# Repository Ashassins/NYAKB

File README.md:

# NYAKB: Not Your Average Keyboard
ECE 477 Project

NYAKB is a multimedia keyboard with hot swappable modules to enable flexibility for the users by allowing them to select the right keyboard layout for the task at hand. The product features a base keyboard with a familiar form factor, as well as modules which can be added and removed with a standard hot plug connector without interrupting the functionality of the rest of the keyboard. We will be making a display module and in the future other modules such as macropads, numpads, or rotary encoders could be added using the same connector to extend the functionality of the keyboard.

Project Website: https://engineering.purdue.edu/477grp3/

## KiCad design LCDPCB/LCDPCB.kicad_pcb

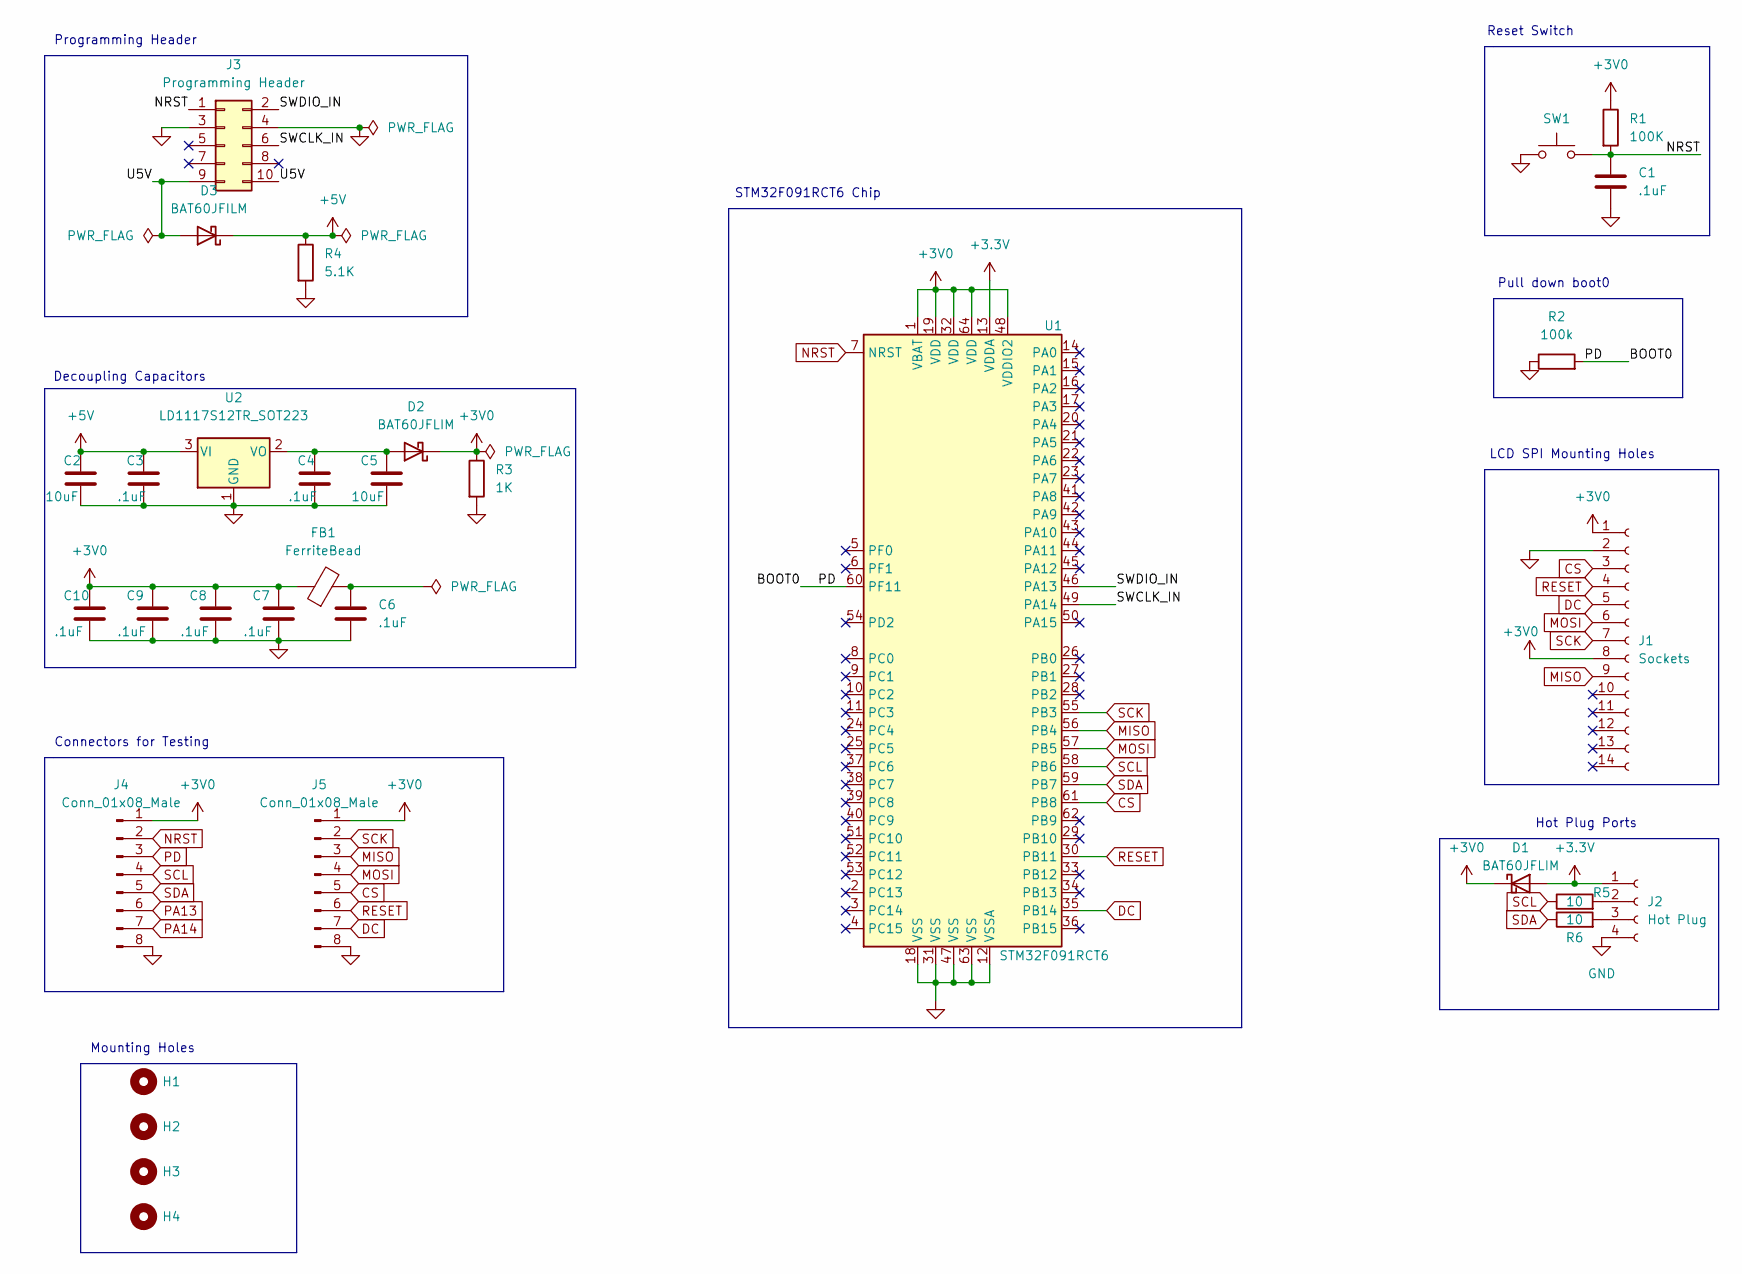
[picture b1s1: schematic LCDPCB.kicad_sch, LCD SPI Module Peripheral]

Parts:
C1, C3, C4, C6, C7, C8, C9, C10: .1uF
C2: 10uF; new10uf
C5: 10uF
D1, D2: BAT60JFLIM; BAT60JFILM
D3: BAT60JFILM
FB1: FerriteBead; Ferrite
H1, H2, H3, H4: MountingHole; MountingHole_2.2mm_M2_ISO7380
J1: Sockets; PinSocket_1x14_P2.54mm_Vertical
J2: Hot Plug; PinSocket_1x04_P2.54mm_Vertical
J3: Programming Header; PinSocket_2x05_P2.54mm_Vertical
J4, J5: Conn_01x08_Male; PinHeader_1x08_P2.54mm_Vertical
R1: 100K; 100k
R2: 100k
R3: 1K; 1k
R4: 5.1K; 5.1k
R5, R6: 10; 10R
SW1: SW_Push; Button
U1: STM32F091RCT6; STM32F091
U2: LD1117S12TR_SOT223; SOT-223-3_TabPin2

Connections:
+3.3V: D1.2 (A), J2.1, U1.13 (VDDA)
+3V0: C7.1, C8.1, C9.1, C10.1, D1.1 (K), D2.1 (K), FB1.1, J1.1, J1.8, J4.1, J5.1, R1.1, R3.1, U1.1 (VBAT), U1.19 (VDD), U1.32 (VDD), U1.48 (VDDIO2), U1.64 (VDD)
+5V: C2.1, C3.1, D3.1 (K), R4.1, U2.3 (VI)
/SWCLK_IN: J3.6, U1.49 (PA14)
/SWDIO_IN: J3.2, U1.46 (PA13)
/U5V: D3.2 (A), J3.9, J3.10
CS: J1.3, J5.5, U1.61 (PB8)
DC: J1.5, J5.7, U1.35 (PB14)
GND: C1.2, C2.2, C3.2, C4.2, C5.2, C6.2, C7.2, C8.2, C9.2, C10.2, J1.2, J2.4, J3.3, J3.4, J4.8, J5.8, R2.1, R3.2, R4.2, SW1.1, U1.12 (VSSA), U1.18 (VSS), U1.31 (VSS), U1.47 (VSS), U1.63 (VSS), U2.1 (GND)
MISO: J1.9, J5.3, U1.56 (PB4)
MOSI: J1.6, J5.4, U1.57 (PB5)
NRST: C1.1, J3.1, J4.2, R1.2, SW1.2, U1.7 (NRST)
unnamed: C4.1, C5.1, D2.2 (A), U2.2 (VO)
unnamed: C6.1, FB1.2
unnamed: J2.2, R5.2
unnamed: J2.3, R6.2
PA13: J4.6
PA14: J4.7
PD: J4.3, R2.2, U1.60 (PF11)
RESET: J1.4, J5.6, U1.30 (PB11)
SCK: J1.7, J5.2, U1.55 (PB3)
SCL: J4.4, R5.1, U1.58 (PB6)
SDA: J4.5, R6.1, U1.59 (PB7)

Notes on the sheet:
Mounting Holes
Reset Switch
STM32F091RCT6 Chip
Programming Header
Connectors for Testing
Pull down boot0
Decoupling Capacitors
Hot Plug Ports
LCD SPI Mounting Holes

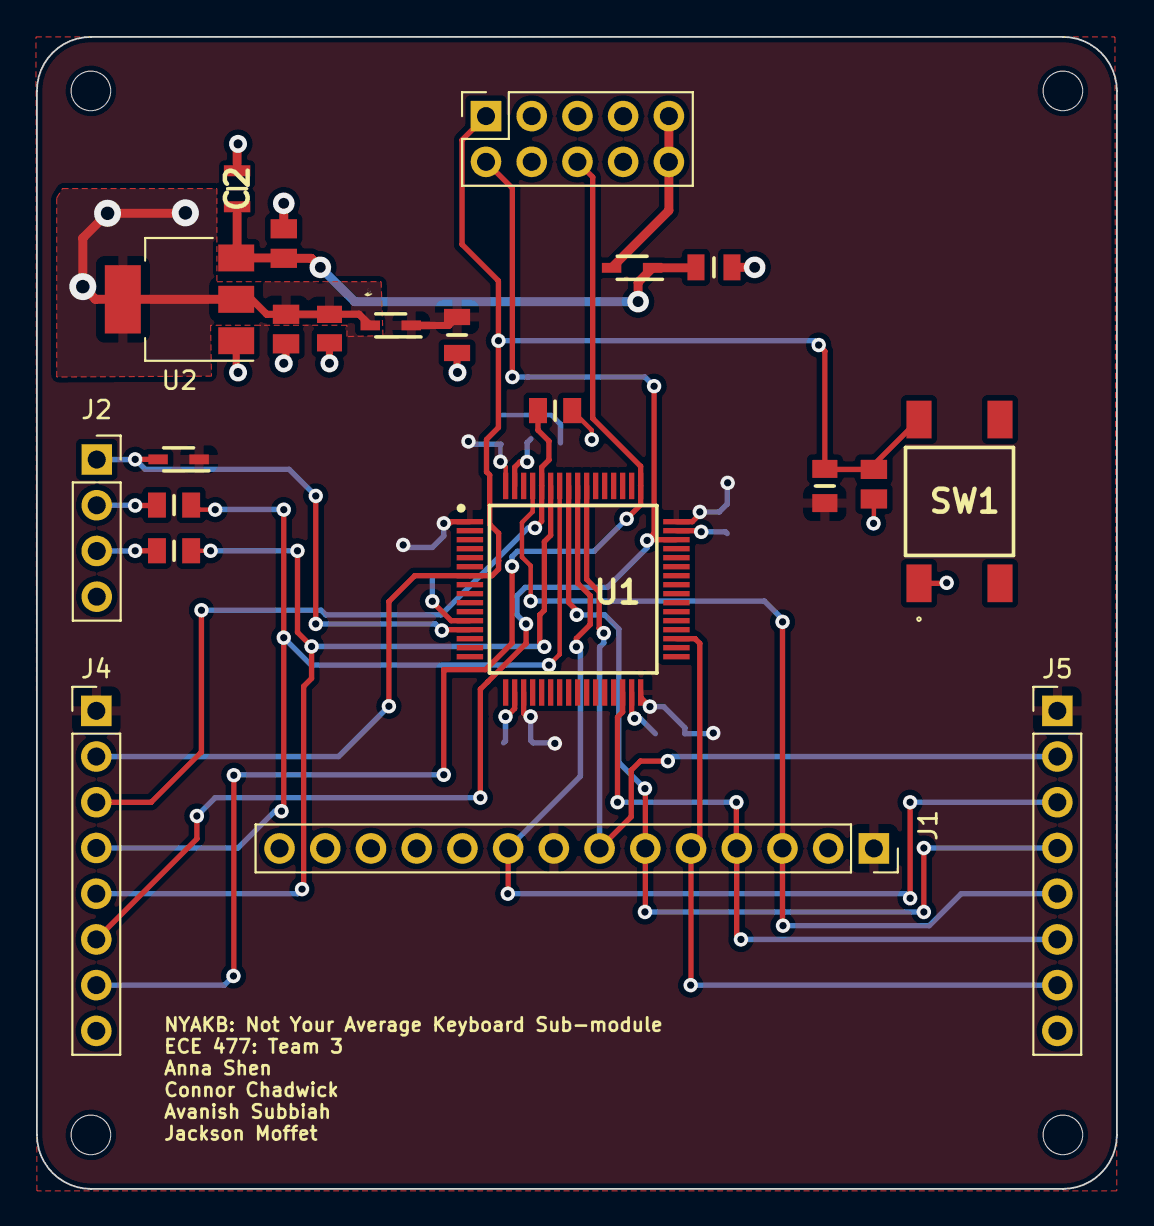
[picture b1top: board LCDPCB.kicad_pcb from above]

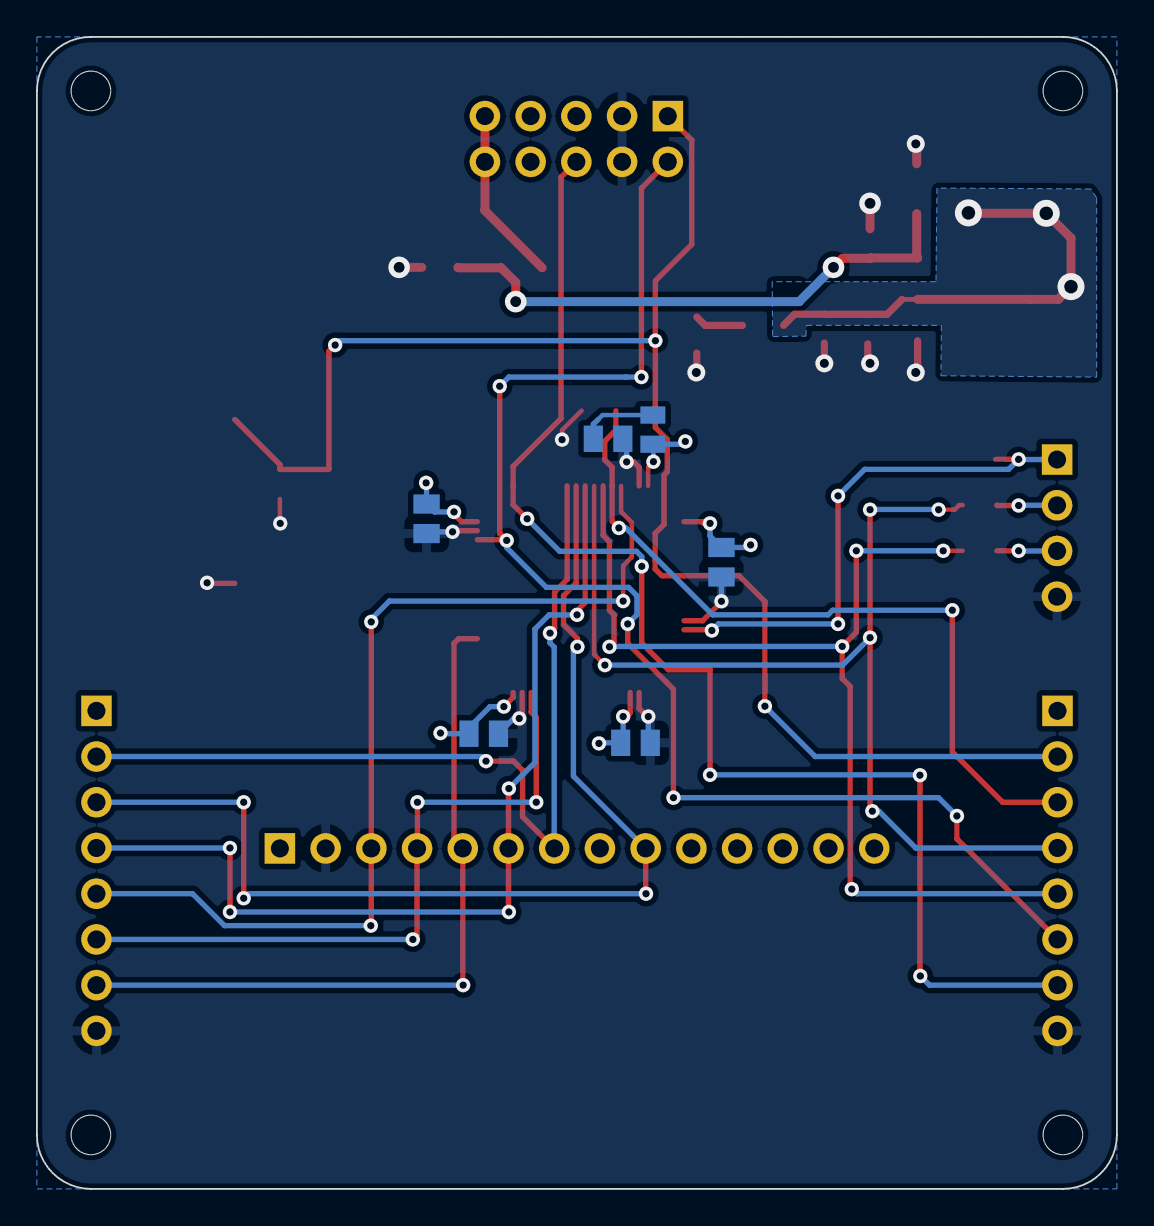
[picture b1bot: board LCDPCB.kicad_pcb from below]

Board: 2 copper layers, 60.0 x 64.0 mm, 32 parts (6 on the bottom side), 21 nets.

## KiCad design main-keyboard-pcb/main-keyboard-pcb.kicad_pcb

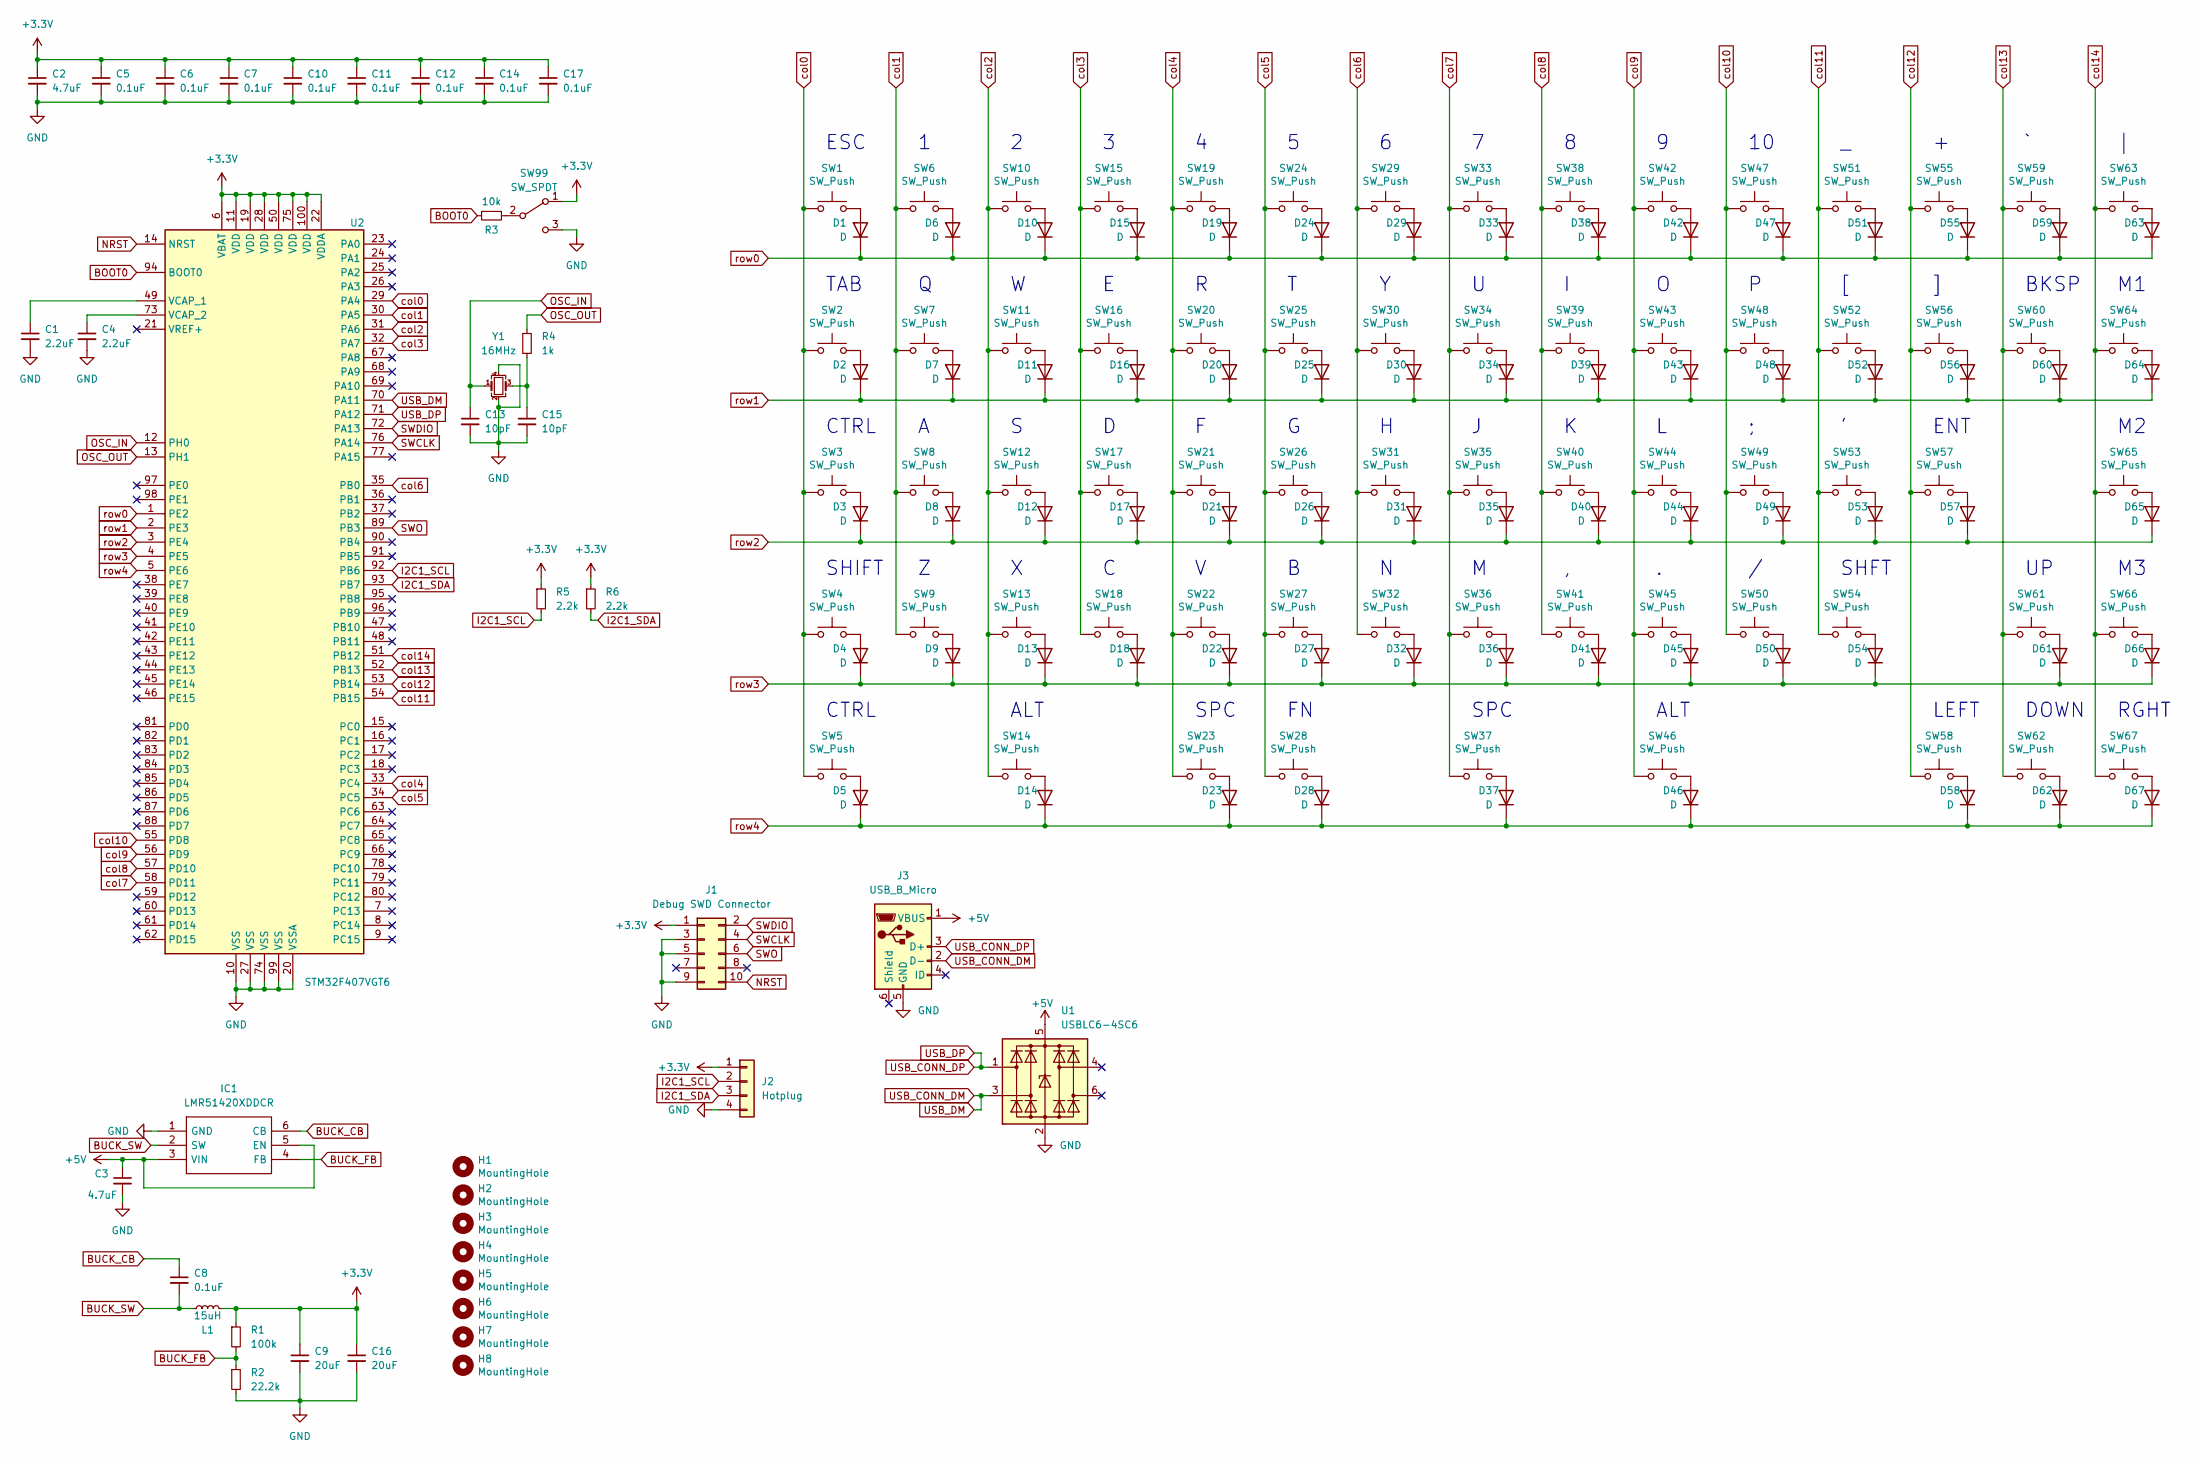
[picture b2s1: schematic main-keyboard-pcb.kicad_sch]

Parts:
C1, C4: 2.2uF; GRM155R61E225KE11D
C2, C3: 4.7uF; GRM188R61C475KAAJD
C5, C6, C7, C8, C10, C11, C12, C14, C17: 0.1uF; GRM022R61A104ME01L
C9, C16: 20uF; GRMJN7R61C206ME05D
C13, C15: 10pF; GRM0225C1C100FA03L
D1, D2, D3, D4, D5, D6, D7, D8, D9, D10, D11, D12, D13, D14, D15, D16, D17, D18, D19, D20, D21, D22, D23, D24, D25, D26, D27, D28, D29, D30, D31, D32, D33, D34, D35, D36, D37, D38, D39, D40, D41, D42, D43, D44, D45, D46, D47, D48, D49, D50, D51, D52, D53, D54, D55, D56, D57, D58, D59, D60, D61, D62, D63, D64, D65, D66, D67: D; 1N4148W-13-F
H1, H2, H3, H4, H5, H6, H7, H8: MountingHole; MountingHole_2.2mm_M2_Pad
IC1: LMR51420XDDCR; Manufacturer_Part_Number LMR51420XDDCR
J1: Debug SWD Connector; PinHeader_2x05_P1.27mm_Vertical_SMD
J2: Hotplug; PinHeader_1x04_P2.54mm_Vertical
J3: USB_B_Micro; USB307530A
L1: 15uH; SRP1265WA150M
R1: 100k; CHV1206AJW-104ELF
R2: 22.2k; ERJP08F2212V
R3: 10k; ERJ-UP3F1002V
R4: 1k; ERJ-UP3D1001V
R5, R6: 2.2k; ERJ-UP3F2201V
SW1, SW6, SW7, SW8, SW9, SW10, SW11, SW12, SW13, SW15, SW16, SW17, SW18, SW19, SW20, SW21, SW22, SW24, SW25, SW26, SW27, SW28, SW29, SW30, SW31, SW32, SW33, SW34, SW35, SW36, SW38, SW39, SW40, SW41, SW42, SW43, SW44, SW45, SW47, SW48, SW49, SW50, SW51, SW52, SW53, SW55, SW56, SW58, SW59, SW61, SW62, SW63, SW64, SW65, SW66, SW67: SW_Push; SW_Cherry_MX_1.00u_PCB
SW2, SW5, SW14, SW46, SW60: SW_Push; SW_Cherry_MX_1.50u_PCB
SW3, SW54: SW_Push; SW_Cherry_MX_1.75u_PCB
SW4: SW_Push; SW_Cherry_MX_2.25u_PCB
SW23: SW_Push; SW_Cherry_MX_2.00u_PCB_ReversedStabilizers
SW37: SW_Push; SW_Cherry_MX_2.75u_PCB_ReversedStabilizers
SW57: SW_Push; SW_Cherry_MX_2.25u_PCB_ReversedStabilizers
SW99: SW_SPDT; SW_SPDT_PCM12
U1: USBLC6-4SC6; SOT-23-6
U2: STM32F407VGT6; LQFP-100_14x14mm_P0.5mm
Y1: 16MHz; ECS-160-10-30B-CKM-TR

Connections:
+3V3: C2.1, C5.1, C6.1, C7.1, C9.1, C10.1, C11.1, C12.1, C14.1, C16.1, C17.1, J1.1, J2.1, L1.2, R1.1, R5.1, R6.1, SW99.1 (A), U2.6 (VBAT), U2.11 (VDD), U2.19 (VDD), U2.22 (VDDA), U2.28 (VDD), U2.50 (VDD), U2.75 (VDD), U2.100 (VDD)
+5V: C3.1, IC1.3 (VIN), IC1.5 (EN), J3.1 (VBUS), U1.5 (VBUS)
BOOT0: R3.2, U2.94 (BOOT0)
BUCK_CB: C8.1, IC1.6 (CB)
BUCK_FB: IC1.4 (FB), R1.2, R2.1
BUCK_SW: C8.2, IC1.2 (SW), L1.1
GND: C1.2, C2.2, C3.2, C4.2, C5.2, C6.2, C7.2, C9.2, C10.2, C11.2, C12.2, C13.2, C14.2, C15.2, C16.2, C17.2, IC1.1 (GND), J1.3, J1.5, J1.9, J2.4, J3.5 (GND), R2.2, SW99.3 (C), U1.2 (GND), U2.10 (VSS), U2.20 (VSSA), U2.27 (VSS), U2.74 (VSS), U2.99 (VSS), Y1.2, Y1.4
I2C1_SCL: J2.2, R5.2, U2.92 (PB6)
I2C1_SDA: J2.3, R6.2, U2.93 (PB7)
NRST: J1.10, U2.14 (NRST)
unnamed: C1.1, U2.49 (VCAP_1)
unnamed: C4.1, U2.73 (VCAP_2)
unnamed: C15.1, R4.2, Y1.3
unnamed: D1.2 (A), SW1.2
unnamed: D2.2 (A), SW2.2
unnamed: D3.2 (A), SW3.2
unnamed: D4.2 (A), SW4.2
unnamed: D5.2 (A), SW5.2
unnamed: D6.2 (A), SW6.2
unnamed: D7.2 (A), SW7.2
unnamed: D8.2 (A), SW8.2
unnamed: D9.2 (A), SW9.2
unnamed: D10.2 (A), SW10.2
unnamed: D11.2 (A), SW11.2
unnamed: D12.2 (A), SW12.2
unnamed: D13.2 (A), SW13.2
unnamed: D14.2 (A), SW14.2
unnamed: D15.2 (A), SW15.2
unnamed: D16.2 (A), SW16.2
unnamed: D17.2 (A), SW17.2
unnamed: D18.2 (A), SW18.2
unnamed: D19.2 (A), SW19.2
unnamed: D20.2 (A), SW20.2
unnamed: D21.2 (A), SW21.2
unnamed: D22.2 (A), SW22.2
unnamed: D23.2 (A), SW23.2
unnamed: D24.2 (A), SW24.2
unnamed: D25.2 (A), SW25.2
unnamed: D26.2 (A), SW26.2
unnamed: D27.2 (A), SW27.2
unnamed: D28.2 (A), SW28.2
unnamed: D29.2 (A), SW29.2
unnamed: D30.2 (A), SW30.2
unnamed: D31.2 (A), SW31.2
unnamed: D32.2 (A), SW32.2
unnamed: D33.2 (A), SW33.2
unnamed: D34.2 (A), SW34.2
unnamed: D35.2 (A), SW35.2
unnamed: D36.2 (A), SW36.2
unnamed: D37.2 (A), SW37.2
unnamed: D38.2 (A), SW38.2
unnamed: D39.2 (A), SW39.2
unnamed: D40.2 (A), SW40.2
unnamed: D41.2 (A), SW41.2
unnamed: D42.2 (A), SW42.2
unnamed: D43.2 (A), SW43.2
unnamed: D44.2 (A), SW44.2
unnamed: D45.2 (A), SW45.2
unnamed: D46.2 (A), SW46.2
unnamed: D47.2 (A), SW47.2
unnamed: D48.2 (A), SW48.2
unnamed: D49.2 (A), SW49.2
unnamed: D50.2 (A), SW50.2
unnamed: D51.2 (A), SW51.2
unnamed: D52.2 (A), SW52.2
unnamed: D53.2 (A), SW53.2
unnamed: D54.2 (A), SW54.2
unnamed: D55.2 (A), SW55.2
unnamed: D56.2 (A), SW56.2
unnamed: D57.2 (A), SW57.2
unnamed: D58.2 (A), SW58.2
unnamed: D59.2 (A), SW59.2
unnamed: D60.2 (A), SW60.2
unnamed: D61.2 (A), SW61.2
unnamed: D62.2 (A), SW62.2
unnamed: D63.2 (A), SW63.2
unnamed: D64.2 (A), SW64.2
unnamed: D65.2 (A), SW65.2
unnamed: D66.2 (A), SW66.2
unnamed: D67.2 (A), SW67.2
unnamed: R3.1, SW99.2 (B)
OSC_IN: C13.1, U2.12 (PH0), Y1.1
OSC_OUT: R4.1, U2.13 (PH1)
SWCLK: J1.4, U2.76 (PA14)
SWDIO: J1.2, U2.72 (PA13)
SWO: J1.6, U2.89 (PB3)
USB_CONN_DM: J3.2 (D-), U1.3 (I/O2), U2.70 (PA11)
USB_CONN_DP: J3.3 (D+), U1.1 (I/O1), U2.71 (PA12)
col0: SW1.1, SW2.1, SW3.1, SW4.1, SW5.1, U2.29 (PA4)
col1: SW6.1, SW7.1, SW8.1, SW9.1, U2.30 (PA5)
col2: SW10.1, SW11.1, SW12.1, SW13.1, SW14.1, U2.31 (PA6)
col3: SW15.1, SW16.1, SW17.1, SW18.1, U2.32 (PA7)
col4: SW19.1, SW20.1, SW21.1, SW22.1, SW23.1, U2.33 (PC4)
col5: SW24.1, SW25.1, SW26.1, SW27.1, SW28.1, U2.34 (PC5)
col6: SW29.1, SW30.1, SW31.1, SW32.1, U2.35 (PB0)
col7: SW33.1, SW34.1, SW35.1, SW36.1, SW37.1, U2.58 (PD11)
col8: SW38.1, SW39.1, SW40.1, SW41.1, U2.57 (PD10)
col9: SW42.1, SW43.1, SW44.1, SW45.1, SW46.1, U2.56 (PD9)
col10: SW47.1, SW48.1, SW49.1, SW50.1, U2.55 (PD8)
col11: SW51.1, SW52.1, SW53.1, SW54.1, U2.54 (PB15)
col12: SW55.1, SW56.1, SW57.1, SW58.1, U2.53 (PB14)
col13: SW59.1, SW60.1, SW61.1, SW62.1, U2.52 (PB13)
col14: SW63.1, SW64.1, SW65.1, SW66.1, SW67.1, U2.51 (PB12)
row0: D1.1 (K), D6.1 (K), D10.1 (K), D15.1 (K), D19.1 (K), D24.1 (K), D29.1 (K), D33.1 (K), D38.1 (K), D42.1 (K), D47.1 (K), D51.1 (K), D55.1 (K), D59.1 (K), D63.1 (K), U2.1 (PE2)
row1: D2.1 (K), D7.1 (K), D11.1 (K), D16.1 (K), D20.1 (K), D25.1 (K), D30.1 (K), D34.1 (K), D39.1 (K), D43.1 (K), D48.1 (K), D52.1 (K), D56.1 (K), D60.1 (K), D64.1 (K), U2.2 (PE3)
row2: D3.1 (K), D8.1 (K), D12.1 (K), D17.1 (K), D21.1 (K), D26.1 (K), D31.1 (K), D35.1 (K), D40.1 (K), D44.1 (K), D49.1 (K), D53.1 (K), D57.1 (K), D65.1 (K), U2.3 (PE4)
row3: D4.1 (K), D9.1 (K), D13.1 (K), D18.1 (K), D22.1 (K), D27.1 (K), D32.1 (K), D36.1 (K), D41.1 (K), D45.1 (K), D50.1 (K), D54.1 (K), D61.1 (K), D66.1 (K), U2.4 (PE5)
row4: D5.1 (K), D14.1 (K), D23.1 (K), D28.1 (K), D37.1 (K), D46.1 (K), D58.1 (K), D62.1 (K), D67.1 (K), U2.5 (PE6)

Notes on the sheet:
TAB
SPC
ESC
RGHT
ALT
ENT
LEFT
BKSP
SHIFT
CTRL
SHFT
DOWN

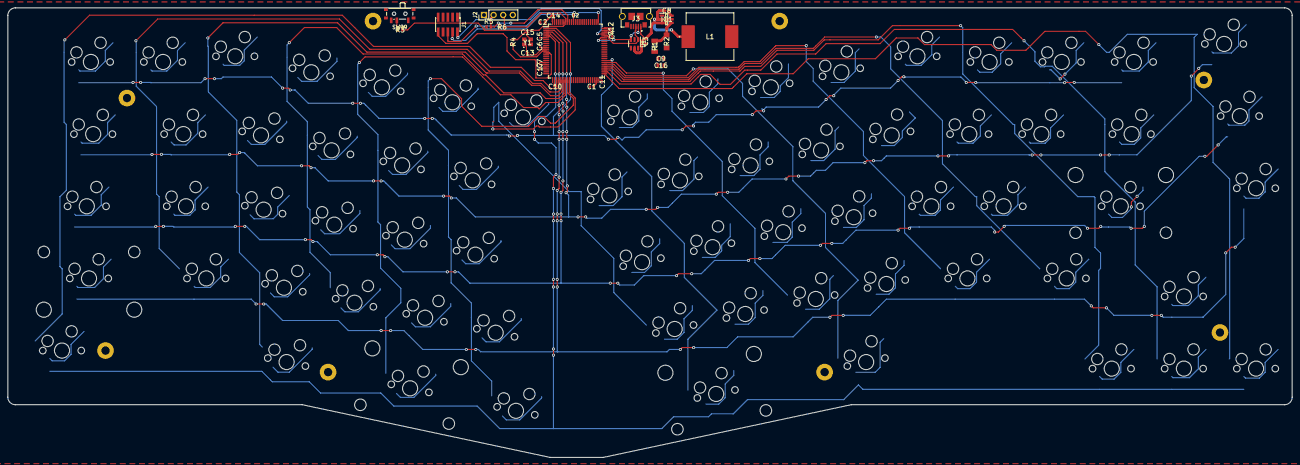
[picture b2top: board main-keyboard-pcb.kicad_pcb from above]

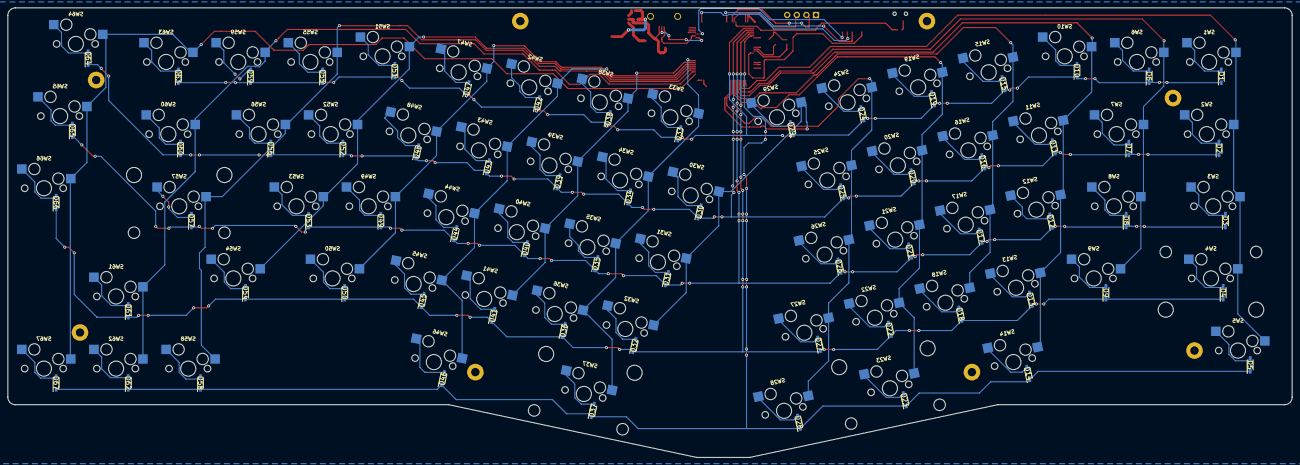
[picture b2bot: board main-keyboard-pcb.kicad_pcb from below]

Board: 4 copper layers, 339.1 x 118.7 mm, 174 parts (67 on the bottom side), 108 nets.

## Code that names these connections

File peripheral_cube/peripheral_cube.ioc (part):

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Mcu.Name=STM32F091R(B-C)Tx
Mcu.Package=LQFP64
Mcu.UserName=STM32F091RCTx
PA13.Mode=Serial_Wire
PA13.Signal=SYS_SWDIO
PA14.Mode=Serial_Wire
PA14.Signal=SYS_SWCLK
PB3.Mode=Full_Duplex_Master
PB3.Signal=SPI1_SCK
PB4.Mode=Full_Duplex_Master
PB4.Signal=SPI1_MISO
PB5.Mode=Full_Duplex_Master
PB5.Signal=SPI1_MOSI
PB8.Signal=GPIO_Output
PF0-OSC_IN.Mode=I2C
PF0-OSC_IN.Signal=I2C1_SDA
PF1-OSC_OUT.Mode=I2C
PF1-OSC_OUT.Signal=I2C1_SCL
RCC.SYSCLKFreq_VALUE=48000000
RCC.SYSCLKSource=RCC_SYSCLKSOURCE_HSI48
board=custom

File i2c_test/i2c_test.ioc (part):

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Mcu.Name=STM32F407V(E-G)Tx
Mcu.Package=LQFP100
Mcu.UserName=STM32F407VGTx
PB6.Mode=I2C
PB6.Signal=I2C1_SCL
PB7.Mode=I2C
PB7.Signal=I2C1_SDA
PH0-OSC_IN.Mode=HSE-External-Oscillator
PH0-OSC_IN.Signal=RCC_OSC_IN
PH1-OSC_OUT.Mode=HSE-External-Oscillator
PH1-OSC_OUT.Signal=RCC_OSC_OUT
RCC.HSE_VALUE=8000000
RCC.SYSCLKFreq_VALUE=168000000
RCC.SYSCLKSource=RCC_SYSCLKSOURCE_PLLCLK
board=custom

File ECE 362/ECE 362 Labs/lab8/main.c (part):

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    RCC->AHBENR |= RCC_AHBENR_GPIOBEN;
    RCC->AHBENR |= RCC_AHBENR_GPIOCEN;

    // GPIOB PB0-10 Outputs
    GPIOB->MODER &= ~0x3FFFFF; // Clear PB0-10
    GPIOB->MODER |= 0x155555;

    // GPIOC PC4-7 Outputs
    GPIOC->MODER &= ~0xFF00;
    GPIOC->MODER |= 0x5500;

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void setup_bb(void) {
    // Enable RCC to GPIOB
    RCC->AHBENR |= RCC_AHBENR_GPIOBEN;
    // Clear PB12,13,15
    GPIOB->MODER &= ~0xCF000000; // Clear PB0-10
    // GPIOB PB12,13,15 Output
    GPIOB->MODER |= 0x45000000;
    // NSS high SCK low
    GPIOB->ODR |= 1<<12;
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void init_spi2(void) {
    // Enable RCC to SPI2
    RCC->APB1ENR |= RCC_APB1ENR_SPI2EN;
    // Enable GPIO Alternate function for PB12,13,15
    // Enable RCC to GPIOB
    RCC->AHBENR |= RCC_AHBENR_GPIOBEN;
    // Clear PB12,13,15
    GPIOB->MODER &= ~0xCF000000; // Clear PB0-10
    // GPIOB PB12,13,15 Alternate Function
    GPIOB->MODER |= 0x8a000000;
    // PB12: AF0
    GPIOB->AFR[1] &= ~(0xf << (4*(12-8)));
    GPIOB->AFR[1] |=   0x0 << (4*(12-8));
    // PB13: AF0
    GPIOB->AFR[1] &= ~(0xf << (4*(13-8)));
    GPIOB->AFR[1] |=   0x0 << (4*(13-8));
    // PB15: AF0
    GPIOB->AFR[1] &= ~(0xf << (4*(15-8)));
    GPIOB->AFR[1] |=   0x0 << (4*(15-8));
    SPI2->CR1 &= ~SPI_CR1_SPE; // Clear CR1_SPE
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void setup_spi1() {
    // Enable RCC to SPI2
    RCC->APB2ENR |= RCC_APB2ENR_SPI1EN;
    // Enable GPIO Alternate function for PB12,13,15
    // Enable RCC to GPIOB
    RCC->AHBENR |= RCC_AHBENR_GPIOAEN;
    // Clear PA5,6,7,15
    GPIOA->MODER &= ~0xc000fc00; // Clear  PA5,6,7,15
    // GPIOB PB12,13,15 Alternate Function
    GPIOA->MODER |= 0x8000a800;
//    // PB5: AF0
//    GPIOB->AFR[1] &= ~(0xf << (4*(5-8)));
//    GPIOB->AFR[1] |=   0x0 << (4*(5-8));
//    // PB6: AF0
//    GPIOB->AFR[1] &= ~(0xf << (4*(13-8)));
//    GPIOB->AFR[1] |=   0x0 << (4*(13-8));
//    // PB15: AF0
//    GPIOB->AFR[1] &= ~(0xf << (4*(15-8)));
//    GPIOB->AFR[1] |=   0x0 << (4*(15-8));
    SPI1->CR1 &= ~SPI_CR1_SPE; // Clear CR1_SPE
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
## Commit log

2022-09-10 Add 362 Reference Files
2022-09-10 Updated .gitignore for STM32CubeIDE
2022-09-10 Added I2C_Test project with i2c3 and otg init
2022-09-10 add some file structure
2022-09-10 isolated debouncing code
2022-09-10 Added GPIO EXTI0 interrupt on Button0 to toggle LED4
2022-09-10 Remove autogen files
2022-09-10 Added I2C send test packet on I2C3
2022-09-10 added the code for the slave
2022-09-19 Update main.c
    Fix mistake
2022-09-19 Update main.c
    Fixed some issues
2022-09-19 code used in slides, I think this would also work however this is configuring the EEPROM and GPIO chip as master and slave, so if we go with this one we will need to rework it to just be the slave
2022-09-20 Remove unused sub-projs
2022-09-20 Update f4 code to tell f0 to toggle led
2022-09-20 Add working peripheral code
2022-09-25 rename F09 kb debouncing file
2022-09-26 updated gitignore for kicad
2022-09-26 Added main-keyboard kicad project
2022-09-26 Added footprints for buck converter
2022-09-26 Added buck converter to schematic
2022-09-27 Working bi-directional comms
2022-09-27 Added buck converter footprints
2022-09-27 add debouncing for f4
2022-09-27 added parts and lcd pcb
2022-09-27 stuff
2022-09-27 added pcb for lcd
2022-09-27 initial state of debouncing f4
2022-09-27 added midterm review
2022-09-27 combine debouncing with main.c in i2c test
2022-09-28 updated with pins
2022-10-03 display done
2022-10-03 design mk 2
2022-10-03 Added Arisu keswitch matrix
2022-10-03 Removed old traces and routing
2022-10-03 Updated diodes
2022-10-04 fixed 1kR
2022-10-04 Completed footprint library for main-keyboard and rough part placement
2022-10-04 Initial routing for stm32f4 and keyswitch matrix
2022-10-04 Routed keyswitch matrix to microcontroller
2022-10-04 Finished initial PCB design, spacing fixes needed
2022-10-04 modify debouncing code to be GPIOE and TIM6 gen
2022-10-04 Updated buck converter design to webench recommendation and updated caps to 0805
2022-10-05 v2 lcd pcb
2022-10-05 Moved over components to 0805 packaging, updated buck converter, added side hotplug connector
2022-10-05 Removed self-intersecting courtyards and added text to components
2022-10-05 Added page info to pcb
2022-10-05 updated pcb text
2022-10-05 cleaned up usb routing
2022-10-05 cleaned up unconnected ends
2022-10-05 added an edit, 3.3V to decoupling capacitor
2022-10-05 minor
2022-10-05 Added labels to boot0 switch and debug vias
2022-10-05 cleaned up row routing and removed unecessary +3V3 vias
2022-10-06 fixed shit
2022-10-06 added thermal relief, made 5V routes wider
2022-10-06 orthoganal
2022-10-07 moved cols to GPIOE and rows to GPIOA
2022-10-07 added thermal reliefs
2022-10-07 updated back silkscreens
2022-10-09 pressed b
2022-10-09 fixed
2022-10-10 do you love me now dad?
2022-10-10 renamed
2022-10-10 Sussy Wussy Poggy Woggy Baddie Daddy UwU
2022-10-12 edits
2022-10-12 remove via from pad v2
2022-10-12 remove via from pads
2022-10-15 Replaced Boot0 with reset sw and created exclusion zone on oscillator
2022-10-15 Updated design constraint copper to edge to 0.03mm
2022-10-16 free of errors
2022-10-16 minor cosmetic change
2022-10-17 Updated exclusion zone to extend to osc_in and osc_out mcu pins
2022-10-17 Beefed up plane connections
2022-10-18 Fixed osc pads and added pull down resistors
2022-10-18 gerber
2022-10-18 added series resistors
2022-10-18 redid gerber
2022-10-18 Added courtyards for hotswap sockets
2022-10-18 move a via
2022-10-18 Fixed differences between sch and pcb
2022-10-18 Fixed via in pad
2022-10-18 Fixed via in pads again
2022-10-18 Fixed trace change error
2022-10-19 added logo
2022-10-19 added drill to gerber
2022-10-19 added drill to main
2022-10-20 drill lcd
2022-10-20 main drill
2022-10-23 Added basic python noti reading
2022-10-23 add mini project files
2022-10-23 cleaning up file structure
2022-10-25 Add peripheral lcd stuff
2022-10-25 Add some necessary project files
2022-10-26 small change to peripheral
2022-10-30 merge
2022-11-01 possibly finished debouncing? Cube hates me or it doesnt work
2022-11-01 remove mini proj on this branch
2022-11-01 Work on enumeration / sending HID packets
2022-11-01 Remove .cproject from .gitignore
2022-11-01 Fix .gitignore
2022-11-01 Add .cproject
2022-11-01 lcd update
2022-11-01 Get past startup by ignoring USB and i2c temporarily
2022-11-01 Readded peripheral project files
2022-11-01 Fix for new i2c controller
2022-11-01 Remove Zone.Identifier files
2022-11-04 Got 75% black screen to display, but still broky
2022-11-05 Fix SysTick / EXTI interrupt level conflict and send the right keycode
2022-11-15 submodule casing files
2022-11-16 Reconfigured for 24MHz clock
2022-11-16 Updated IOC
2022-11-17 normal peripheral
2022-11-17 renamed pa13 and 14
2022-11-17 Added cube spi
2022-11-17 Add peripheral_cube test code
2022-11-17 add semi-colon
2022-11-17 Force add project files
2022-11-17 Prescale down from 4mhz to 32khz
2022-11-17 Remove test
2022-11-17 Push 'ported' lcd driver
2022-11-17 Configure pin B8 as output
2022-11-17 Hello World working on SPI
2022-11-18 Attempt 1 at i2c comms
2022-11-18 i2c bitbang attempt 1 irregular clock issue
2022-11-30 Working code for checkoff i2c comms
2022-11-30 Working code for checkoff i2c comms (peripheral)
2022-12-01 Added empty keyscanning funcs
2022-12-01 Update ioc and clocks
2022-12-01 Added f key send every 5 seconds
2022-12-01 new case
2022-12-03 starting point for QMK style debouncing
2022-12-03 add keymap
2022-12-03 remove unnecessary ifdefs from quantum.h
2022-12-03 add timer_avr.h
2022-12-06 added i2c refactor
2022-12-06 First pass at implementing key scanning
2022-12-06 Export i2c functions
2022-12-06 Prep demo
2022-12-08 Check in progress
2022-12-10 Well at least it works....
2022-12-10 Add explanitory comments to keyboard decoding
2022-12-11 Fix i2c to not wedge on single byte coms
2022-12-12 Magic string violates all common sense
